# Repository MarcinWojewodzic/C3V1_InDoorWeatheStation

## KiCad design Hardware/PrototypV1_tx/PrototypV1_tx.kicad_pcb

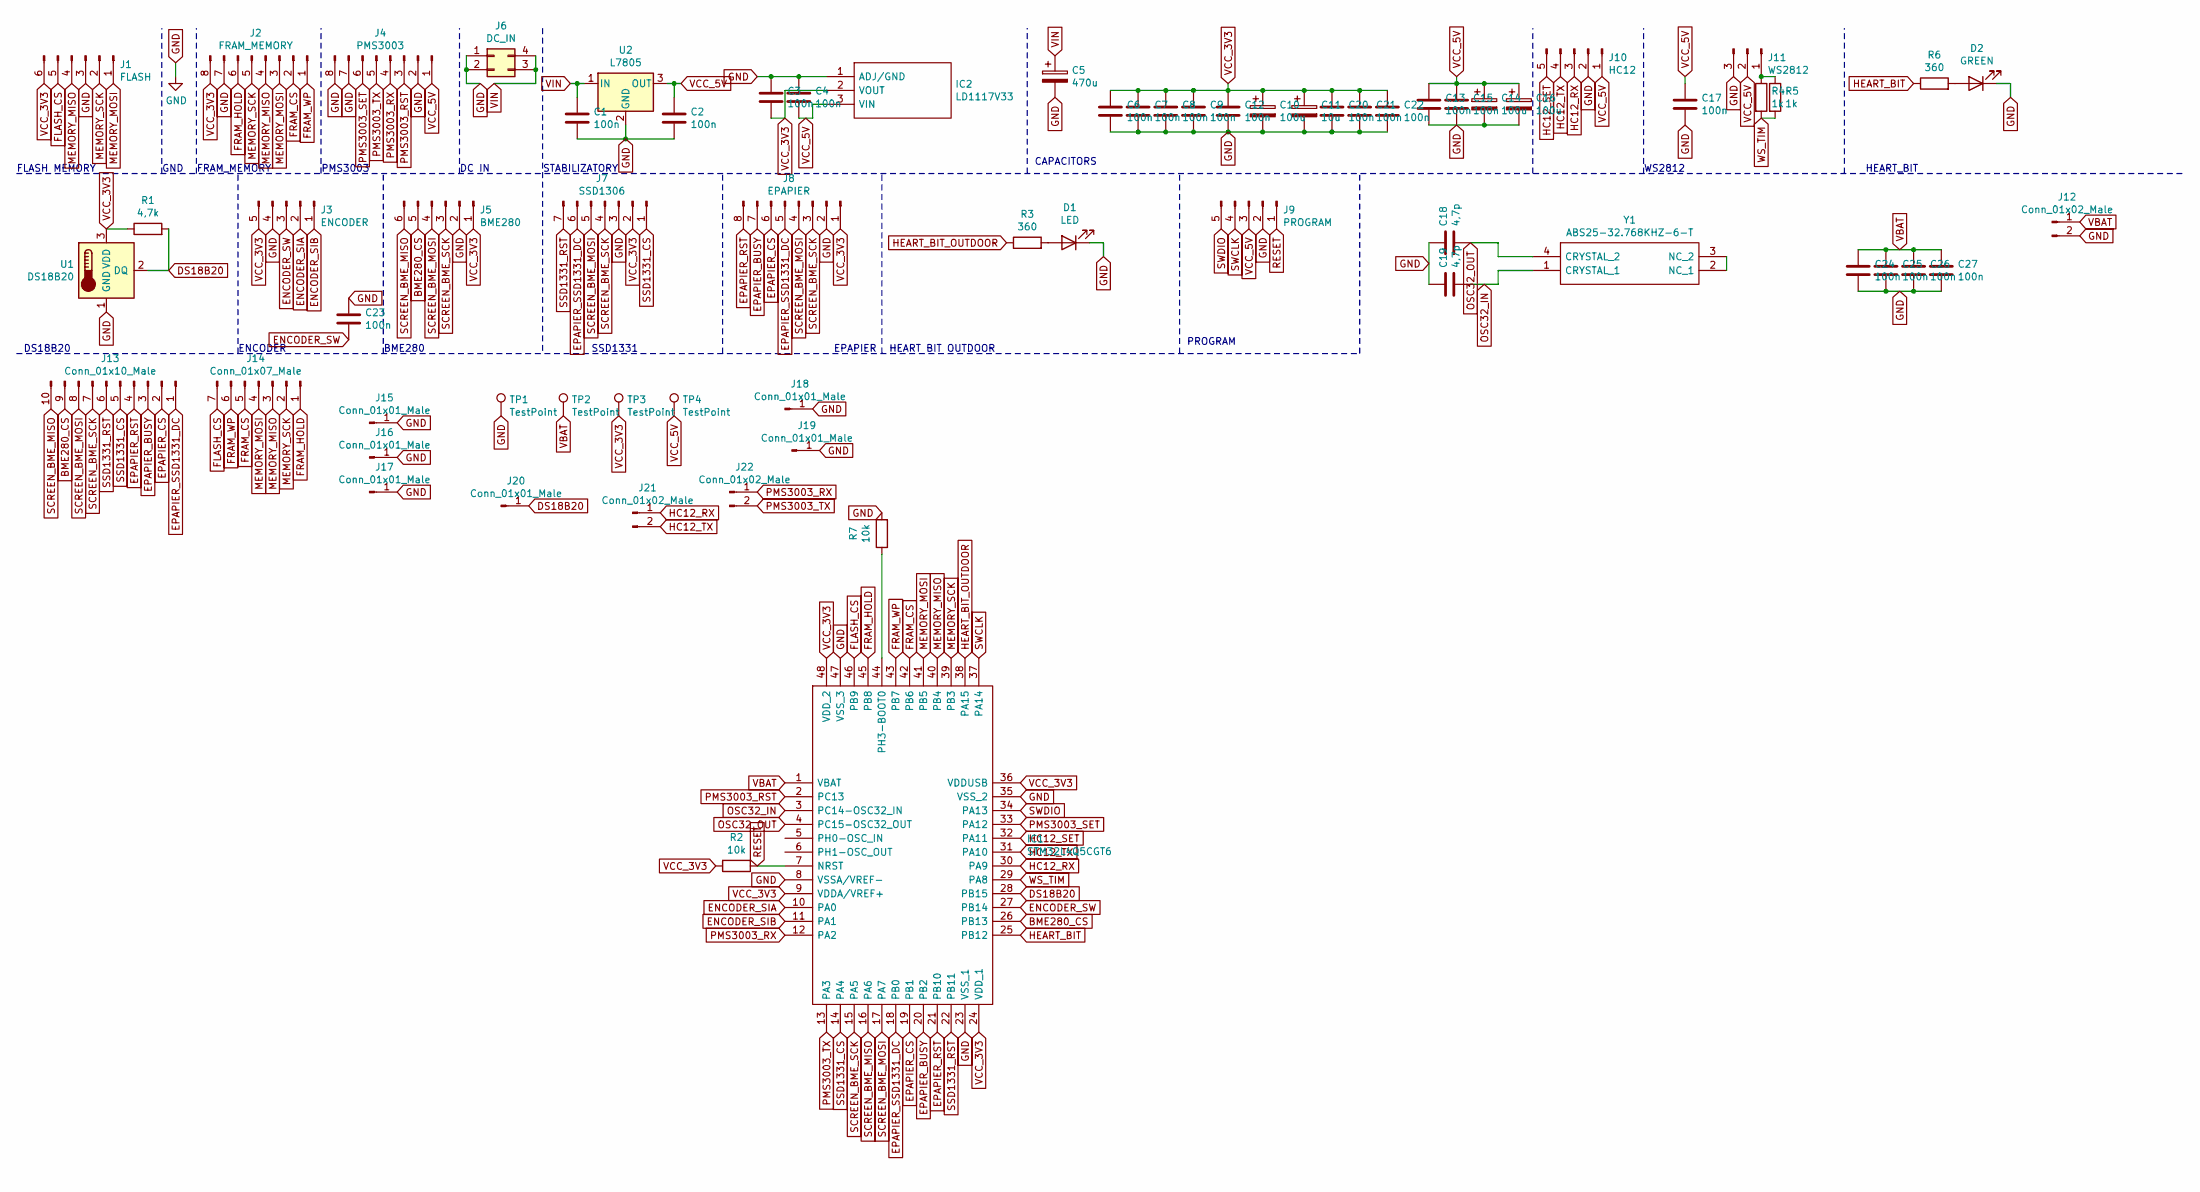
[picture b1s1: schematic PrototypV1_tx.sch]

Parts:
C1, C2, C3, C4, C6, C7, C8, C9, C12, C13, C15, C17, C20, C21, C22, C23, C24, C25, C26, C27: 100n; C_1206_3216Metric_Pad1.33x1.80mm_HandSolder
C5: 470u; CP_Elec_8x10.5
C10, C14, C16: 100u; CP_Elec_5x5.4
C11: 10u; CP_Elec_4x5.4
C18, C19: 4,7p; C_1206_3216Metric_Pad1.33x1.80mm_HandSolder
D1: LED; LED_1206_3216Metric_Pad1.42x1.75mm_HandSolder
D2: GREEN; LED_1206_3216Metric_Pad1.42x1.75mm_HandSolder
IC1: STM32L4Q5CGT6; QFP50P900X900X160-48N; Manufacturer_Part_Number STM32L4Q5CGT6; Mouser Part Number 511-STM32L4Q5CGT6
IC2: LD1117V33; TO-220-3_Vertical; Manufacturer_Part_Number LD1117V33; Mouser Part Number 511-LD1117V33
J1: FLASH; PinHeader_1x06_P2.54mm_Vertical
J2: FRAM_MEMORY; PinHeader_1x08_P2.54mm_Vertical
J3: ENCODER; PinHeader_1x05_P2.54mm_Vertical
J4: PMS3003; PinHeader_1x08_P2.54mm_Vertical
J5: BME280; PinHeader_1x06_P2.54mm_Vertical
J6: DC_IN; PinHeader_2x02_P2.54mm_Vertical
J7: SSD1306; PinSocket_1x07_P2.54mm_Vertical
J8: EPAPIER; PinHeader_1x08_P2.54mm_Vertical
J9: PROGRAM; PinHeader_1x05_P2.54mm_Vertical
J10: HC12; PinHeader_1x05_P2.54mm_Vertical
J11: WS2812; PinHeader_1x03_P2.54mm_Vertical
J12, J21, J22: Conn_01x02_Male; PinHeader_1x02_P2.54mm_Vertical
J13: Conn_01x10_Male; PinHeader_1x10_P2.54mm_Vertical
J14: Conn_01x07_Male; PinHeader_1x07_P2.54mm_Vertical
J15, J16, J17, J18, J19, J20: Conn_01x01_Male; PinHeader_1x01_P2.54mm_Vertical
R1: 4,7k; R_1206_3216Metric_Pad1.30x1.75mm_HandSolder
R2, R7: 10k; R_1206_3216Metric_Pad1.30x1.75mm_HandSolder
R3, R6: 360; R_1206_3216Metric_Pad1.30x1.75mm_HandSolder
R4, R5: 1k; R_1206_3216Metric_Pad1.30x1.75mm_HandSolder
TP1, TP2, TP3, TP4: TestPoint; TestPoint_Pad_2.0x2.0mm
U1: DS18B20; TO-92_Inline
U2: L7805; TO-220-3_Vertical
Y1: ABS25-32.768KHZ-6-T; ABS2532768KHZT; Manufacturer_Part_Number ABS25-32.768KHZ-6-T; Mouser Part Number 815-ABS25-32.768K6-T

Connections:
BME280_CS: IC1.26 (PB13), J5.5, J13.9
DS18B20: IC1.28 (PB15), J20.1, R1.2, U1.2 (DQ)
ENCODER_SIA: IC1.10 (PA0), J3.2
ENCODER_SIB: IC1.11 (PA1), J3.1
ENCODER_SW: C23.2, IC1.27 (PB14), J3.3
EPAPIER_BUSY: IC1.20 (PB2), J8.7, J13.3
EPAPIER_CS: IC1.19 (PB1), J8.6, J13.2
EPAPIER_RST: IC1.21 (PB10), J8.8, J13.4
EPAPIER_SSD1331_DC: IC1.18 (PB0), J7.6, J8.5, J13.1
FLASH_CS: IC1.46 (PB9), J1.5, J14.7
FRAM_CS: IC1.42 (PB6), J2.2, J14.5
FRAM_HOLD: IC1.45 (PB8), J2.6, J14.1
FRAM_WP: IC1.43 (PB7), J2.1, J14.6
GND: C1.2, C2.2, C3.1, C4.1, C5.2, C6.2, C7.2, C8.2, C9.2, C10.2, C11.2, C12.2, C13.2, C14.2, C15.2, C16.2, C17.2, C18.1, C19.1, C20.2, C21.2, C22.2, C23.1, C24.2, C25.2, C26.2, C27.2, D1.1 (K), D2.1 (K), IC1.8 (VSSA/VREF-), IC1.23 (VSS_1), IC1.35 (VSS_2), IC1.47 (VSS_3), IC2.1 (ADJ/GND), J1.3, J2.7, J3.4, J4.2, J4.7, J4.8, J5.2, J6.1, J6.2, J7.3, J8.2, J9.2, J10.2, J11.3, J12.2, J15.1, J16.1, J17.1, J18.1, J19.1, R7.2, TP1.1, U1.1 (GND), U2.2 (GND)
HC12_RX: IC1.30 (PA9), J10.3, J21.1
HC12_SET: IC1.32 (PA11), J10.5
HC12_TX: IC1.31 (PA10), J10.4, J21.2
HEART_BIT: IC1.25 (PB12), R6.1
HEART_BIT_OUTDOOR: IC1.38 (PA15), R3.1
MEMORY_MISO: IC1.40 (PB4), J1.4, J2.4, J14.3
MEMORY_MOSI: IC1.41 (PB5), J1.1, J2.3, J14.4
MEMORY_SCK: IC1.39 (PB3), J1.2, J2.5, J14.2
unnamed: D1.2 (A), R3.2
unnamed: D2.2 (A), R6.2
unnamed: IC1.44 (PH3-BOOT0), R7.1
unnamed: J11.1, R4.1, R5.1
unnamed: Y1.2 (NC_1), Y1.3 (NC_2)
OSC32_IN: C19.2, IC1.3 (PC14-OSC32_IN), Y1.1 (CRYSTAL_1)
OSC32_OUT: C18.2, IC1.4 (PC15-OSC32_OUT), Y1.4 (CRYSTAL_2)
PMS3003_RST: IC1.2 (PC13), J4.3
PMS3003_RX: IC1.12 (PA2), J4.4, J22.1
PMS3003_SET: IC1.33 (PA12), J4.6
PMS3003_TX: IC1.13 (PA3), J4.5, J22.2
RESET: IC1.7 (NRST), J9.1, R2.1
SCREEN_BME_MISO: IC1.16 (PA6), J5.6, J13.10
SCREEN_BME_MOSI: IC1.17 (PA7), J5.4, J7.5, J8.4, J13.8
SCREEN_BME_SCK: IC1.15 (PA5), J5.3, J7.4, J8.3, J13.7
SSD1331_CS: IC1.14 (PA4), J7.1, J13.5
SSD1331_RST: IC1.22 (PB11), J7.7, J13.6
SWCLK: IC1.37 (PA14), J9.4
SWDIO: IC1.34 (PA13), J9.5
VBAT: C24.1, C25.1, C26.1, C27.1, IC1.1 (VBAT), J12.1, TP2.1
VCC_3V3: C3.2, C6.1, C7.1, C8.1, C9.1, C10.1, C11.1, C12.1, C20.1, C21.1, C22.1, IC1.9 (VDDA/VREF+), IC1.24 (VDD_1), IC1.36 (VDDUSB), IC1.48 (VDD_2), IC2.2 (VOUT), J1.6, J2.8, J3.5, J5.1, J7.2, J8.1, R1.1, R2.2, TP3.1, U1.3 (VDD)
VCC_5V: C2.1, C4.2, C13.1, C14.1, C15.1, C16.1, C17.1, IC2.3 (VIN), J4.1, J9.3, J10.1, J11.2, TP4.1, U2.3 (OUT)
VIN: C1.1, C5.1, J6.3, J6.4, U2.1 (IN)
WS_TIM: IC1.29 (PA8), R4.2, R5.2

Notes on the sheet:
FLASH MEMORY
GND
FRAM_MEMORY
PMS3003
DC IN
STABILIZATORY
CAPACITORS
WS2812
HEART_BIT
DS18B20
ENCODER
BME280
SSD1331
EPAPIER
HEART BIT OUTDOOR
PROGRAM

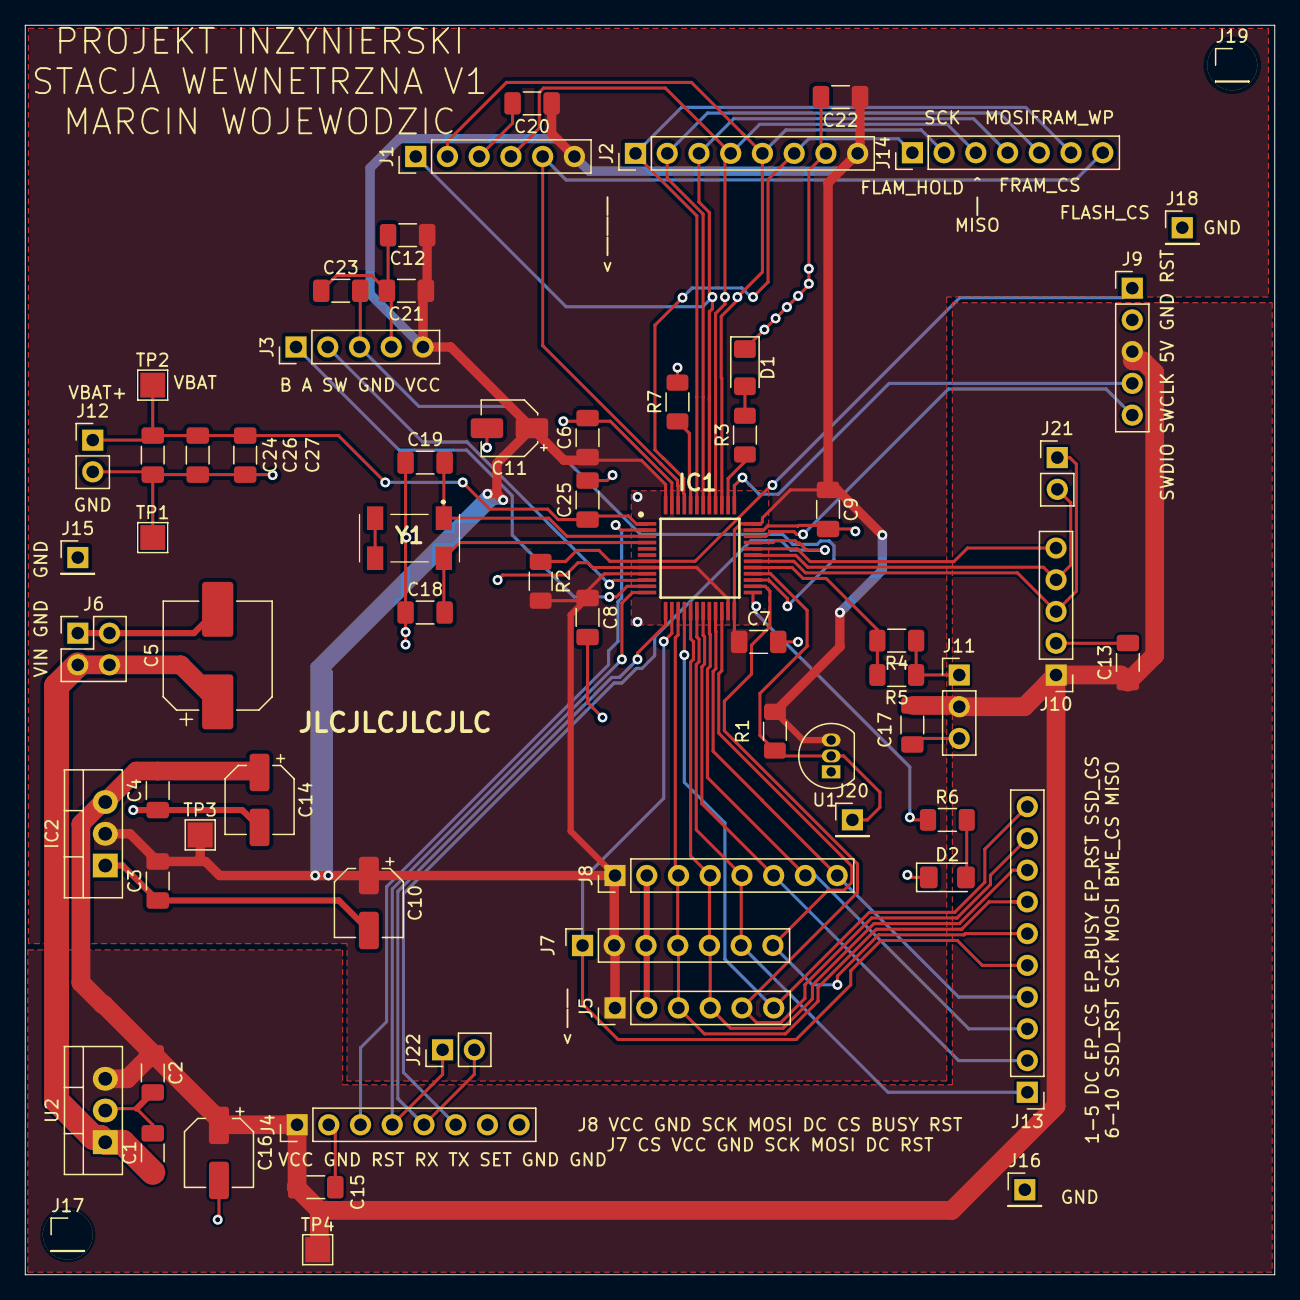
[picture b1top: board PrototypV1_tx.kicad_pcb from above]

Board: 2 copper layers, 100.0 x 100.0 mm, 67 parts (0 on the bottom side), 46 nets.

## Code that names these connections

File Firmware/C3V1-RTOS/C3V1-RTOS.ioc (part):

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Mcu.Name=STM32L4P5C(G-E)Tx
Mcu.Package=LQFP48
Mcu.UserName=STM32L4P5CGTx
PA0.Signal=S_TIM5_CH1
PA1.Signal=S_TIM5_CH2
PA10.Mode=Asynchronous
PA10.Signal=USART1_RX
PA11.GPIOParameters=GPIO_Label
PA11.GPIO_Label=HC12_SET
PA11.Signal=GPIO_Output
PA12.GPIOParameters=GPIO_Speed,PinState,GPIO_Label
PA12.GPIO_Label=PMS3003_RST
PA12.GPIO_Speed=GPIO_SPEED_FREQ_VERY_HIGH
PA12.PinState=GPIO_PIN_SET
PA12.Signal=GPIO_Output
PA13\ (JTMS/SWDIO).Mode=Serial_Wire
PA13\ (JTMS/SWDIO).Signal=SYS_JTMS-SWDIO
PA14\ (JTCK/SWCLK).Mode=Serial_Wire
PA14\ (JTCK/SWCLK).Signal=SYS_JTCK-SWCLK
PA15\ (JTDI).GPIOParameters=GPIO_Speed,GPIO_Label
PA15\ (JTDI).GPIO_Label=SIGNAL
PA15\ (JTDI).GPIO_Speed=GPIO_SPEED_FREQ_VERY_HIGH
PA15\ (JTDI).Signal=GPIO_Output
PA2.Mode=Asynchronous
PA2.Signal=USART2_TX
PA3.Mode=Asynchronous
PA3.Signal=USART2_RX
PA4.GPIOParameters=GPIO_Speed,PinState,GPIO_Label
PA4.GPIO_Label=SSD1306_CS
PA4.GPIO_Speed=GPIO_SPEED_FREQ_VERY_HIGH
PA4.PinState=GPIO_PIN_SET
PA4.Signal=GPIO_Output
PA5.Mode=Full_Duplex_Master
PA5.Signal=SPI1_SCK
PA6.Mode=Full_Duplex_Master
PA6.Signal=SPI1_MISO
PA7.Mode=Full_Duplex_Master
PA7.Signal=SPI1_MOSI
PA8.Signal=S_TIM1_CH1
PA9.Mode=Asynchronous
PA9.Signal=USART1_TX
PB0.GPIOParameters=GPIO_Speed,PinState,GPIO_Label
PB0.GPIO_Label=SCREENS_DC
PB0.GPIO_Speed=GPIO_SPEED_FREQ_VERY_HIGH
PB0.PinState=GPIO_PIN_SET
PB0.Signal=GPIO_Output
PB1.GPIOParameters=GPIO_Speed,PinState,GPIO_Label
PB1.GPIO_Label=EPAPIER_CS
PB1.GPIO_Speed=GPIO_SPEED_FREQ_VERY_HIGH
PB1.PinState=GPIO_PIN_SET
PB1.Signal=GPIO_Output
PB10.GPIOParameters=GPIO_Speed,PinState,GPIO_Label
PB10.GPIO_Label=EPAPIER_RST
PB10.GPIO_Speed=GPIO_SPEED_FREQ_VERY_HIGH
PB10.PinState=GPIO_PIN_SET
PB10.Signal=GPIO_Output
PB11.GPIOParameters=GPIO_Speed,PinState,GPIO_Label
PB11.GPIO_Label=SSD1306_RST
PB11.GPIO_Speed=GPIO_SPEED_FREQ_VERY_HIGH
PB11.PinState=GPIO_PIN_SET
PB11.Signal=GPIO_Output
PB12.GPIOParameters=GPIO_Speed,GPIO_Label
PB12.GPIO_Label=HEARTBEAT
PB12.GPIO_Speed=GPIO_SPEED_FREQ_VERY_HIGH
PB12.Signal=GPIO_Output
PB13.GPIOParameters=GPIO_Label
PB13.GPIO_Label=BME280_CS
PB13.Signal=GPIO_Output
PB14.GPIOParameters=GPIO_Label
PB14.GPIO_Label=ENCODER_SWITCH
PB14.Signal=GPIO_Input
PB15.GPIOParameters=GPIO_Speed,PinState,GPIO_Label
PB15.GPIO_Label=PMS3003_SET
PB15.GPIO_Speed=GPIO_SPEED_FREQ_VERY_HIGH
PB15.PinState=GPIO_PIN_SET
PB15.Signal=GPIO_Output
PB2.GPIOParameters=GPIO_Label
PB2.GPIO_Label=EPAPIER_BUSY
PB2.Signal=GPIO_Input
PB6.GPIOParameters=GPIO_Speed,PinState,GPIO_Label
PB6.GPIO_Label=FRAM_CS
PB6.GPIO_Speed=GPIO_SPEED_FREQ_VERY_HIGH
PB6.PinState=GPIO_PIN_SET
PB6.Signal=GPIO_Output
PB7.GPIOParameters=GPIO_Speed,PinState,GPIO_Label
PB7.GPIO_Label=FRAM_WP
PB7.GPIO_Speed=GPIO_SPEED_FREQ_VERY_HIGH
PB7.PinState=GPIO_PIN_SET
PB7.Signal=GPIO_Output
PB8.GPIOParameters=GPIO_Label
PB8.GPIO_Label=FRAM_HOLD
PB8.Signal=GPIO_Output
PB9.GPIOParameters=GPIO_Speed,PinState,GPIO_Label
PB9.GPIO_Label=FLASH_CS
PB9.GPIO_Speed=GPIO_SPEED_FREQ_VERY_HIGH
PB9.PinState=GPIO_PIN_SET
PB9.Signal=GPIO_Output
PC14-OSC32_IN\ (PC14).Mode=LSE-External-Oscillator
PC14-OSC32_IN\ (PC14).Signal=RCC_OSC32_IN
PC15-OSC32_OUT\ (PC15).Mode=LSE-External-Oscillator
PC15-OSC32_OUT\ (PC15).Signal=RCC_OSC32_OUT
RCC.HSE_VALUE=8000000
RCC.SYSCLKFreq_VALUE=120000000
RCC.SYSCLKSource=RCC_SYSCLKSOURCE_PLLCLK
board=custom

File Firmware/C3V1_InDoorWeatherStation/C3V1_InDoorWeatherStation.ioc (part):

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Mcu.Name=STM32L4P5C(G-E)Tx
Mcu.Package=LQFP48
Mcu.UserName=STM32L4P5CGTx
PA0.Signal=S_TIM5_CH1
PA1.Signal=S_TIM5_CH2
PA10.Mode=Asynchronous
PA10.Signal=USART1_RX
PA11.GPIOParameters=PinState,GPIO_Label
PA11.GPIO_Label=HC12_SET
PA11.PinState=GPIO_PIN_SET
PA11.Signal=GPIO_Output
PA12.GPIOParameters=GPIO_Label
PA12.GPIO_Label=PMS_SET
PA12.Signal=GPIO_Output
PA13\ (JTMS/SWDIO).Mode=Serial_Wire
PA13\ (JTMS/SWDIO).Signal=SYS_JTMS-SWDIO
PA14\ (JTCK/SWCLK).Mode=Serial_Wire
PA14\ (JTCK/SWCLK).Signal=SYS_JTCK-SWCLK
PA2.Mode=Asynchronous
PA2.Signal=USART2_TX
PA3.Mode=Asynchronous
PA3.Signal=USART2_RX
PA4.GPIOParameters=GPIO_Speed,PinState,GPIO_Label
PA4.GPIO_Label=SSD1306_CS
PA4.GPIO_Speed=GPIO_SPEED_FREQ_VERY_HIGH
PA4.PinState=GPIO_PIN_SET
PA4.Signal=GPIO_Output
PA5.Mode=Full_Duplex_Master
PA5.Signal=SPI1_SCK
PA6.Mode=Full_Duplex_Master
PA6.Signal=SPI1_MISO
PA7.Mode=Full_Duplex_Master
PA7.Signal=SPI1_MOSI
PA8.Signal=S_TIM1_CH1
PA9.Mode=Asynchronous
PA9.Signal=USART1_TX
PB0.GPIOParameters=GPIO_Speed,PinState,GPIO_Label
PB0.GPIO_Label=SCREENS_DC
PB0.GPIO_Speed=GPIO_SPEED_FREQ_VERY_HIGH
PB0.PinState=GPIO_PIN_SET
PB0.Signal=GPIO_Output
PB1.GPIOParameters=GPIO_Speed,PinState,GPIO_Label
PB1.GPIO_Label=EPAPIER_CS
PB1.GPIO_Speed=GPIO_SPEED_FREQ_VERY_HIGH
PB1.PinState=GPIO_PIN_SET
PB1.Signal=GPIO_Output
PB10.GPIOParameters=GPIO_Speed,PinState,GPIO_Label
PB10.GPIO_Label=EPAPIER_RST
PB10.GPIO_Speed=GPIO_SPEED_FREQ_VERY_HIGH
PB10.PinState=GPIO_PIN_SET
PB10.Signal=GPIO_Output
PB11.GPIOParameters=GPIO_Speed,PinState,GPIO_Label
PB11.GPIO_Label=SSD1306_RST
PB11.GPIO_Speed=GPIO_SPEED_FREQ_VERY_HIGH
PB11.PinState=GPIO_PIN_SET
PB11.Signal=GPIO_Output
PB12.GPIOParameters=GPIO_Label
PB12.GPIO_Label=HEARTBEAT
PB12.Signal=GPIO_Output
PB13.GPIOParameters=GPIO_Speed,PinState,GPIO_Label
PB13.GPIO_Label=BME280_CS
PB13.GPIO_Speed=GPIO_SPEED_FREQ_VERY_HIGH
PB13.PinState=GPIO_PIN_SET
PB13.Signal=GPIO_Output
PB14.GPIOParameters=GPIO_Label
PB14.GPIO_Label=ENCODER_SWITCH
PB14.Signal=GPIO_Input
PB15.GPIOParameters=GPIO_Label
PB15.GPIO_Label=DS18B20
PB15.Signal=GPIO_Output
PB2.GPIOParameters=GPIO_Label
PB2.GPIO_Label=EPAPIER_BUSY
PB2.Signal=GPIO_Input
PB6.GPIOParameters=GPIO_Speed,PinState,GPIO_Label
PB6.GPIO_Label=FRAM_CS
PB6.GPIO_Speed=GPIO_SPEED_FREQ_VERY_HIGH
PB6.PinState=GPIO_PIN_SET
PB6.Signal=GPIO_Output
PB7.GPIOParameters=GPIO_Speed,PinState,GPIO_Label
PB7.GPIO_Label=FRAM_WP
PB7.GPIO_Speed=GPIO_SPEED_FREQ_VERY_HIGH
PB7.PinState=GPIO_PIN_SET
PB7.Signal=GPIO_Output
PB8.GPIOParameters=GPIO_Speed,PinState,GPIO_Label
PB8.GPIO_Label=FRAM_HOLD
PB8.GPIO_Speed=GPIO_SPEED_FREQ_VERY_HIGH
PB8.PinState=GPIO_PIN_SET
PB8.Signal=GPIO_Output
PB9.GPIOParameters=GPIO_Speed,PinState,GPIO_Label
PB9.GPIO_Label=FLASH_CS
PB9.GPIO_Speed=GPIO_SPEED_FREQ_VERY_HIGH
PB9.PinState=GPIO_PIN_SET
PB9.Signal=GPIO_Output
PC13.GPIOParameters=GPIO_Label
PC13.GPIO_Label=PMS_RST
PC13.Signal=GPIO_Output
PC14-OSC32_IN\ (PC14).Mode=LSE-External-Oscillator
PC14-OSC32_IN\ (PC14).Signal=RCC_OSC32_IN
PC15-OSC32_OUT\ (PC15).Mode=LSE-External-Oscillator
PC15-OSC32_OUT\ (PC15).Signal=RCC_OSC32_OUT
RCC.HSE_VALUE=8000000
RCC.SYSCLKFreq_VALUE=40000000
RCC.SYSCLKSource=RCC_SYSCLKSOURCE_PLLCLK
board=custom

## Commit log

2022-12-20 Podstawa RTOS
2022-12-24 Dodano BME280, odbiór, wysyłanie komend i wyświetlanie
2023-01-03 Dodano zmianę godziny z przycisku
2023-01-07 Dodano zapis i odczyt NIE TESTOWANY JESZCZE
2023-01-09 Dodano Wyświetlanie Wykresów
2023-01-15 Projekt ukończony w 99%
2023-01-15 Ukończono
2023-01-19 Naprawiono błąd z wykresami
2023-01-27 Naprawiono błąd z zapisem danych
